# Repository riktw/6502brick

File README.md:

# 6502brick
A 6502 dev board usable with multiple popular projects

This board features a 65C02 CPU, 32K RAM, 32K ROM (16K mapped by default), a 65C22 VIA and a MC6850 ACIA.
A 40 pin header is available with address, data and control signals to extend the board more, or to connect a logic analyzer.
Like Ben Eater's amazing video's, a button is available for single stepping.

The memory map and interrupts are controlled via GALs for flexibility

More information can be read here:  https://justanotherelectronicsblog.com/?p=802

# Memory map:

0x0000 - 0x7FFF		RAM

0x8000 - 0x9FFF		External peripherals

0xA000 - 0xAFFF		MC6850 ACIA for UART

0xB000 - 0xBFFF		65C22 VIA for GPIO + Timers

0xC000 - 0xFFFF		ROM

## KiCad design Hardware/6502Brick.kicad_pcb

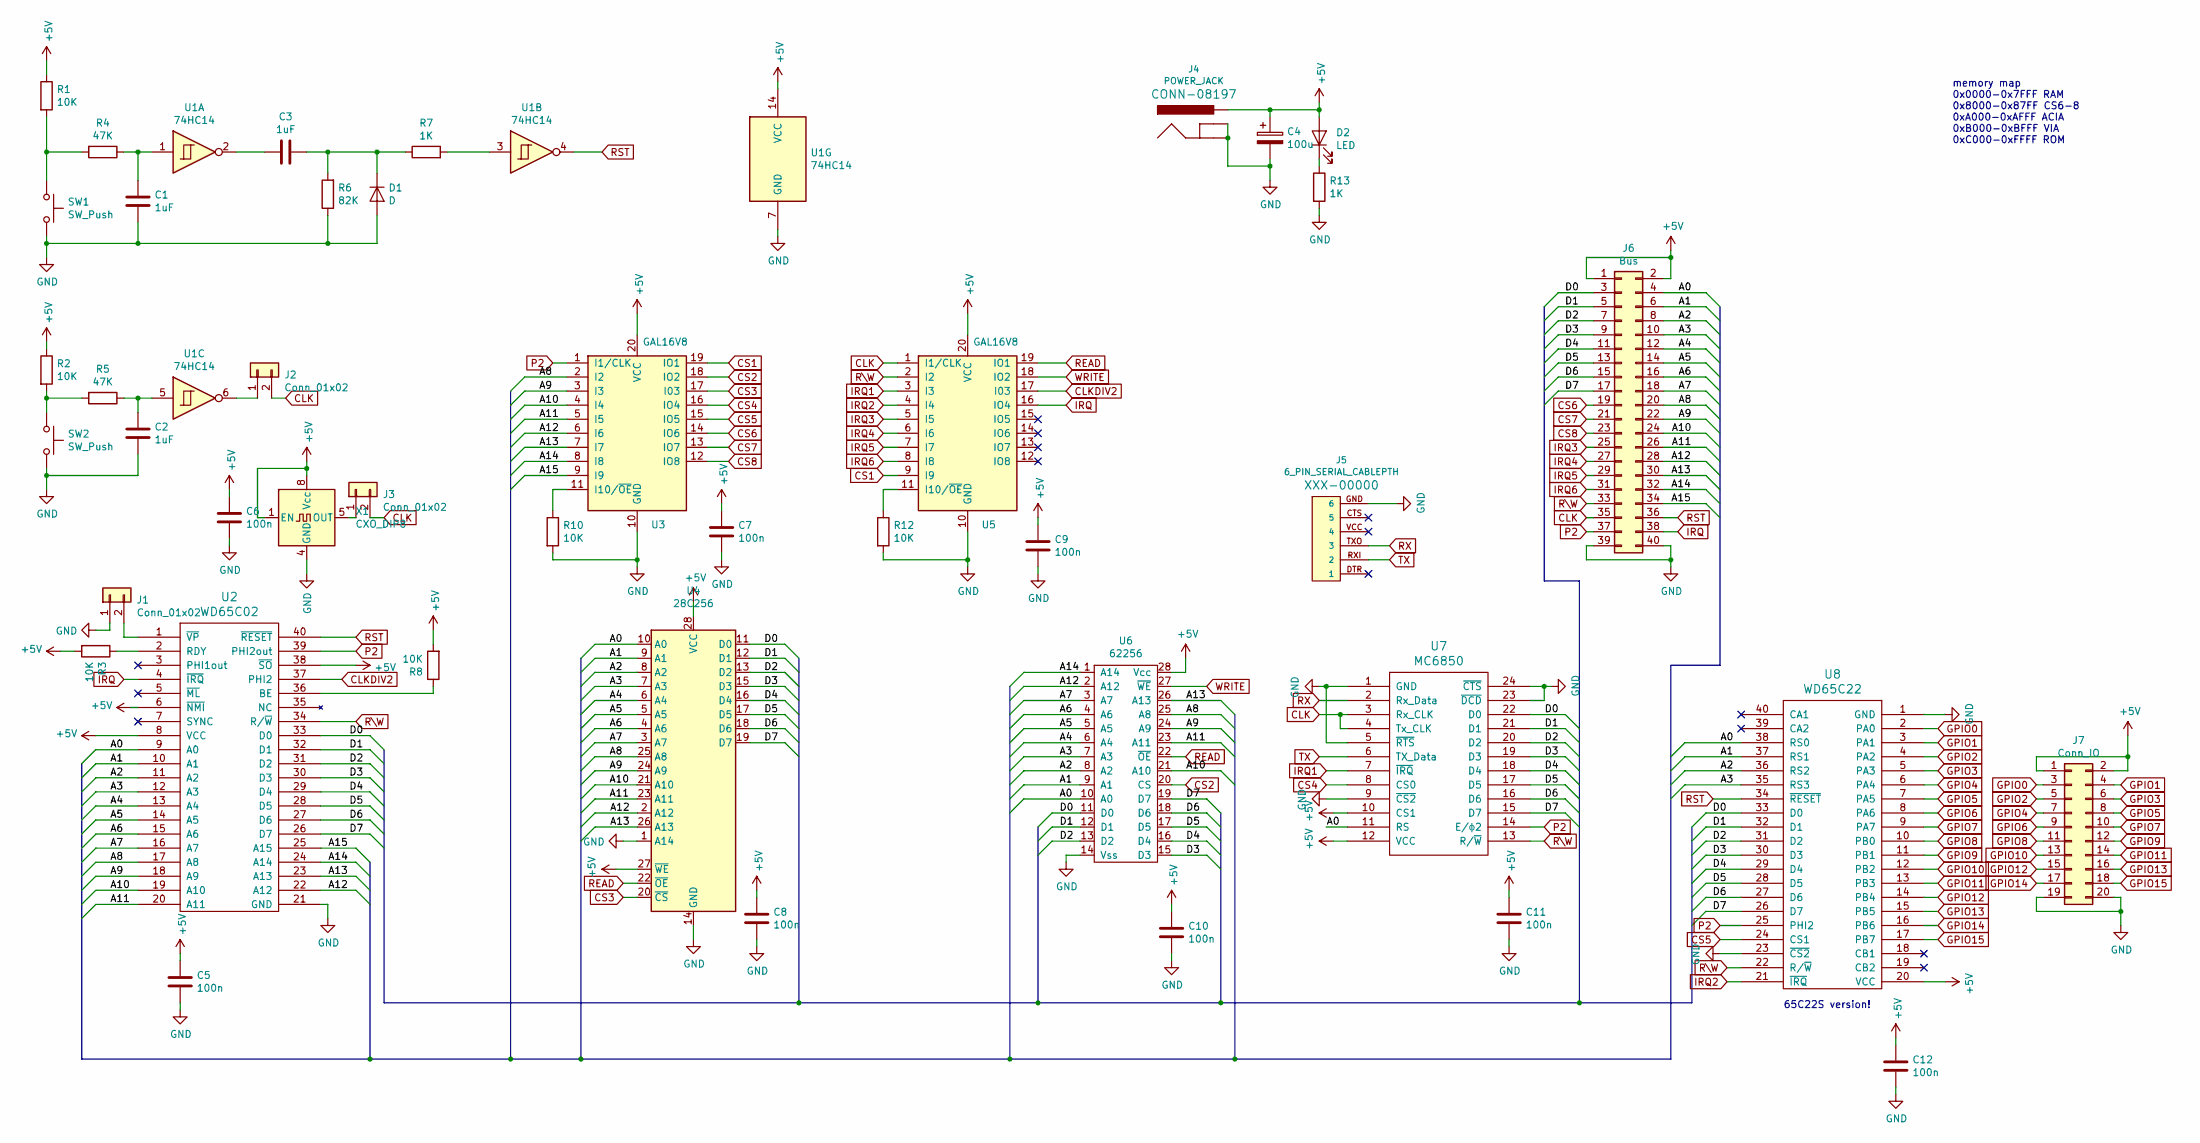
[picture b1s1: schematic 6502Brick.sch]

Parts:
C1, C2, C3: 1uF; C_Rect_L7.0mm_W2.5mm_P5.00mm
C4: 100u; CP_Radial_D5.0mm_P2.00mm
C5, C6, C7, C8, C9, C10, C11, C12: 100n; C_Rect_L7.0mm_W2.5mm_P5.00mm
D1: D; D_DO-34_SOD68_P7.62mm_Horizontal
D2: LED; LED_D5.0mm
J1, J2, J3: Conn_01x02; PinSocket_1x02_P2.54mm_Vertical
J4: POWER_JACK; POWER_JACK_PTH
J5: 6_PIN_SERIAL_CABLEPTH; FTDI_BASIC
J6: Bus; PinSocket_2x20_P2.54mm_Horizontal
J7: Conn_IO; IDC-Header_2x10_P2.54mm_Vertical
R1, R2, R3, R8, R10, R12: 10K; R_Axial_DIN0207_L6.3mm_D2.5mm_P2.54mm_Vertical
R4, R5: 47K; R_Axial_DIN0207_L6.3mm_D2.5mm_P2.54mm_Vertical
R6: 82K; R_Axial_DIN0207_L6.3mm_D2.5mm_P2.54mm_Vertical
R7, R13: 1K; R_Axial_DIN0207_L6.3mm_D2.5mm_P2.54mm_Vertical
SW1, SW2: SW_Push; SW_PUSH_6mm
U1: 74HC14; DIP-14_W7.62mm
U2: WD65C02; DIP-40_W15.24mm_Socket
U3, U5: GAL16V8; DIP-20_W7.62mm_Socket
U4: 28C256; DIP_Socket-28_W11.9_W12.7_W15.24_W17.78_W18.5_3M_228-1277-0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
U6: 62256; DIP-28_W15.24mm_Socket
U7: MC6850; DIP-24_W15.24mm_Socket
U8: WD65C22; DIP-40_W15.24mm_Socket
X1: CXO_DIP8; Oscillator_DIP-8

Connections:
+5V: C4.1, C5.1, C6.1, C7.1, C8.1, C9.1, C10.1, C11.1, C12.1, D2.2 (A), J4.PWR, J6.1, J6.2, J7.1, J7.2, R1.1, R2.1, R3.2, R8.2, U1.14 (VCC), U2.6 (~NMI), U2.8 (VCC), U2.38 (~SO), U3.20 (VCC), U4.27 (~WE), U4.28 (VCC), U5.20 (VCC), U6.28 (Vcc), U7.10 (CS1), U7.12 (VCC), U8.20 (VCC), X1.1 (EN), X1.8 (Vcc)
/A0: J6.4, U2.9 (A0), U4.10 (A0), U6.10 (A0), U7.11 (RS), U8.38 (RS0)
/A1: J6.6, U2.10 (A1), U4.9 (A1), U6.9 (A1), U8.37 (RS1)
/A2: J6.8, U2.11 (A2), U4.8 (A2), U6.8 (A2), U8.36 (RS2)
/A3: J6.10, U2.12 (A3), U4.7 (A3), U6.7 (A3), U8.35 (RS3)
/A4: J6.12, U2.13 (A4), U4.6 (A4), U6.6 (A4)
/A5: J6.14, U2.14 (A5), U4.5 (A5), U6.5 (A5)
/A6: J6.16, U2.15 (A6), U4.4 (A6), U6.4 (A6)
/A7: J6.18, U2.16 (A7), U4.3 (A7), U6.3 (A7)
/A8: J6.20, U2.17 (A8), U3.2 (I2), U4.25 (A8), U6.25 (A8)
/A9: J6.22, U2.18 (A9), U3.3 (I3), U4.24 (A9), U6.24 (A9)
/A10: J6.24, U2.19 (A10), U3.4 (I4), U4.21 (A10), U6.21 (A10)
/A11: J6.26, U2.20 (A11), U3.5 (I5), U4.23 (A11), U6.23 (A11)
/A12: J6.28, U2.22 (A12), U3.6 (I6), U4.2 (A12), U6.2 (A12)
/A13: J6.30, U2.23 (A13), U3.7 (I7), U4.26 (A13), U6.26 (A13)
/A14: J6.32, U2.24 (A14), U3.8 (I8), U6.1 (A14)
/A15: J6.34, U2.25 (A15), U3.9 (I9)
/D0: J6.3, U2.33 (D0), U4.11 (D0), U6.11 (D0), U7.22 (D0), U8.33 (D0)
/D1: J6.5, U2.32 (D1), U4.12 (D1), U6.12 (D1), U7.21 (D1), U8.32 (D1)
/D2: J6.7, U2.31 (D2), U4.13 (D2), U6.13 (D2), U7.20 (D2), U8.31 (D2)
/D3: J6.9, U2.30 (D3), U4.15 (D3), U6.15 (D3), U7.19 (D3), U8.30 (D3)
/D4: J6.11, U2.29 (D4), U4.16 (D4), U6.16 (D4), U7.18 (D4), U8.29 (D4)
/D5: J6.13, U2.28 (D5), U4.17 (D5), U6.17 (D5), U7.17 (D5), U8.28 (D5)
/D6: J6.15, U2.27 (D6), U4.18 (D6), U6.18 (D6), U7.16 (D6), U8.27 (D6)
/D7: J6.17, U2.26 (D7), U4.19 (D7), U6.19 (D7), U7.15 (D7), U8.26 (D7)
CLK: J2.2, J3.2, J6.35, U5.1 (I1/CLK), U7.3 (Rx_CLK), U7.4 (Tx_CLK)
CLKDIV2: U2.37 (PHI2), U5.17 (I03)
CS1: U3.19 (IO1), U5.9 (I9)
CS2: U3.18 (IO2), U6.20 (CS)
CS3: U3.17 (I03), U4.20 (~CS)
CS4: U3.16 (IO4), U7.8 (CS0)
CS5: U3.15 (IO5), U8.24 (CS1)
CS6: J6.19, U3.14 (IO6)
CS7: J6.21, U3.13 (IO7)
CS8: J6.23, U3.12 (IO8)
GND: C1.2, C2.2, C4.2, C5.2, C6.2, C7.2, C8.2, C9.2, C10.2, C11.2, C12.2, D1.2 (A), J1.1, J4.GND, J4.GNDB (GNDBREAK), J5.GND (6), J6.39, J6.40, J7.19, J7.20, R6.1, R10.2, R12.2, R13.2, SW1.2, SW2.2, U1.7 (GND), U2.21 (GND), U3.10 (GND), U4.1 (A14), U4.14 (GND), U5.10 (GND), U6.14 (Vss), U7.1 (GND), U7.5 (~RTS), U7.9 (~CS2), U7.23 (~DCD), U7.24 (~CTS), U8.1 (GND), U8.23 (~CS2), X1.4 (GND)
GPIO0: J7.3, U8.2 (PA0)
GPIO1: J7.4, U8.3 (PA1)
GPIO2: J7.5, U8.4 (PA2)
GPIO3: J7.6, U8.5 (PA3)
GPIO4: J7.7, U8.6 (PA4)
GPIO5: J7.8, U8.7 (PA5)
GPIO6: J7.9, U8.8 (PA6)
GPIO7: J7.10, U8.9 (PA7)
GPIO8: J7.11, U8.10 (PB0)
GPIO9: J7.12, U8.11 (PB1)
GPIO10: J7.13, U8.12 (PB2)
GPIO11: J7.14, U8.13 (PB3)
GPIO12: J7.15, U8.14 (PB4)
GPIO13: J7.16, U8.15 (PB5)
GPIO14: J7.17, U8.16 (PB6)
GPIO15: J7.18, U8.17 (PB7)
IRQ: J6.38, U2.4 (~IRQ), U5.16 (IO4)
IRQ1: U5.3 (I3), U7.7 (~IRQ)
IRQ2: U5.4 (I4), U8.21 (~IRQ)
IRQ3: J6.25, U5.5 (I5)
IRQ4: J6.27, U5.6 (I6)
IRQ5: J6.29, U5.7 (I7)
IRQ6: J6.31, U5.8 (I8)
unnamed: C1.1, R4.1, U1.1
unnamed: C2.1, R5.1, U1.5
unnamed: C3.1, D1.1 (K), R6.2, R7.1
unnamed: C3.2, U1.2
unnamed: D2.1 (K), R13.1
unnamed: J1.2, U2.1 (~VP)
unnamed: J2.1, U1.6
unnamed: J3.1, X1.5 (OUT)
unnamed: R1.2, R4.2, SW1.1
unnamed: R2.2, R5.2, SW2.1
unnamed: R3.1, U2.2 (RDY)
unnamed: R7.2, U1.3
unnamed: R8.1, U2.36 (BE)
unnamed: R10.1, U3.11 (I10/~OE~)
unnamed: R12.1, U5.11 (I10/~OE~)
P2: J6.37, U2.39 (PHI2out), U3.1 (I1/CLK), U7.14 (E/ϕ2), U8.25 (PHI2)
READ: U4.22 (~OE), U5.19 (IO1), U6.22 (~OE)
RST: J6.36, U1.4, U2.40 (~RESET), U8.34 (~RESET)
RX: J5.TXO (3), U7.2 (Rx_Data)
R\W: J6.33, U2.34 (R/~W), U5.2 (I2), U7.13 (R/~W), U8.22 (R/~W)
TX: J5.RXI (2), U7.6 (TX_Data)
WRITE: U5.18 (IO2), U6.27 (~WE)

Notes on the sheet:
65C22S version!
memory map 0x0000-0x7FFF RAM 0x8000-0x87FF CS6-8 0xA000-0xAFFF ACIA 0xB000-0xBFFF VIA 0xC000-0xFFFF ROM

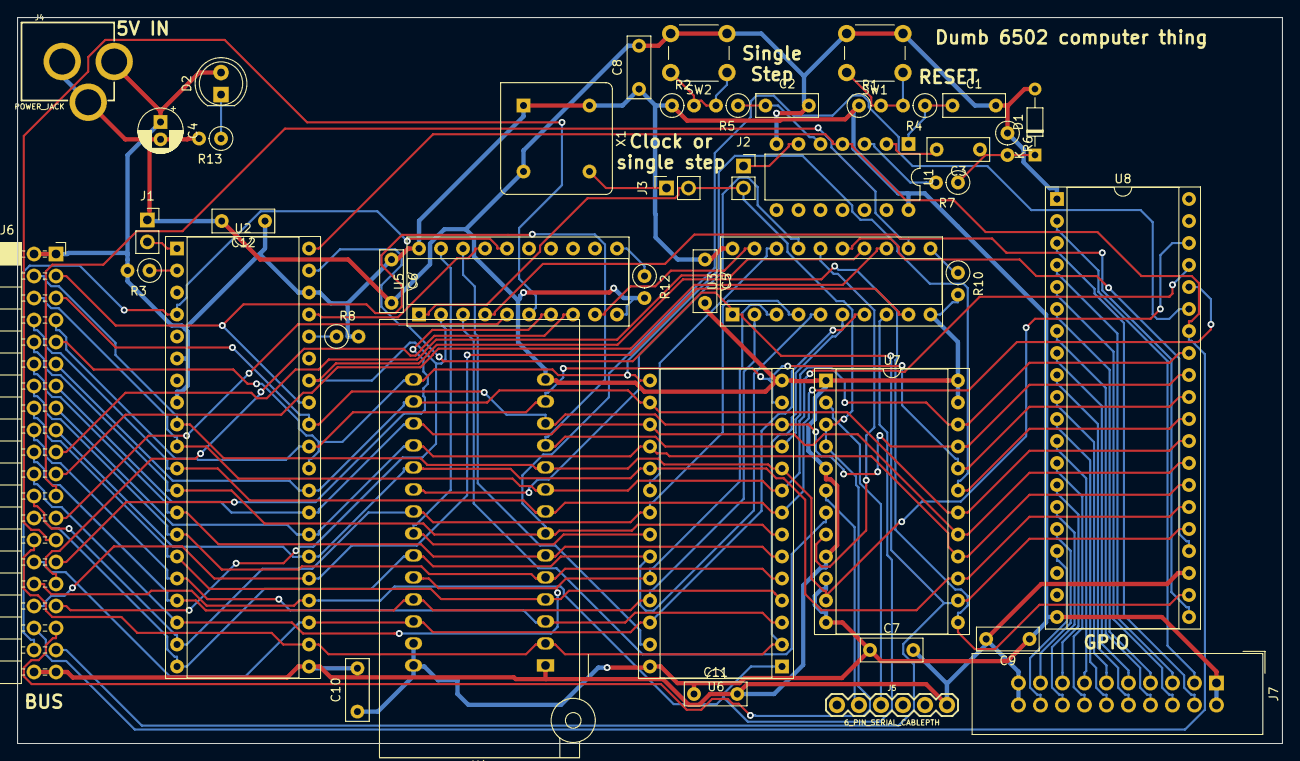
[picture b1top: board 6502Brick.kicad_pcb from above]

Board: 2 copper layers, 146.0 x 83.8 mm, 43 parts (0 on the bottom side), 81 nets.

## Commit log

2020-11-09 Initial commit for the project
2020-11-09 Fixed readme
